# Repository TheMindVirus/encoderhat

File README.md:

# SparkFun RGB LED Push Encoder pHAT for Raspberry Pi (encoderphat)

## What is it?
It's an add-on board for the Raspberry Pi single board computer.

It makes use of 3x AVR Microcontrollers working together across I2C.

## What does it do?
It adds 3x customisable knobs with built-in multicoloured lights and push buttons.

It also gives you better access to the Pi's SPI Header Pins and lets you add custom firmware.

## Why do I need one?
It's great for small projects which need analog control, especially for music and science projects.

It can also combine with other HATs to form a keyboard scroller for when a USB keyboard is impractical.

## How do I get one?
It hasn't been released yet at the time of writing. I hope that SparkFun may pick it up and start producing it.

For now, these are my EAGLE design files. You may fork this repository and customise the design before you send it to The Fab.

## Useful Links
RGB LED Push Encoder: https://www.sparkfun.com/products/15141

ATMEGA328P-MU QFN32: https://statics3.seeedstudio.com/images/opl/datasheet/310010005.pdf

What is a Pi HAT?: https://www.raspberrypi.org/blog/introducing-raspberry-pi-hats/

## Enjoy!
Alastair Cota 18/07/2020

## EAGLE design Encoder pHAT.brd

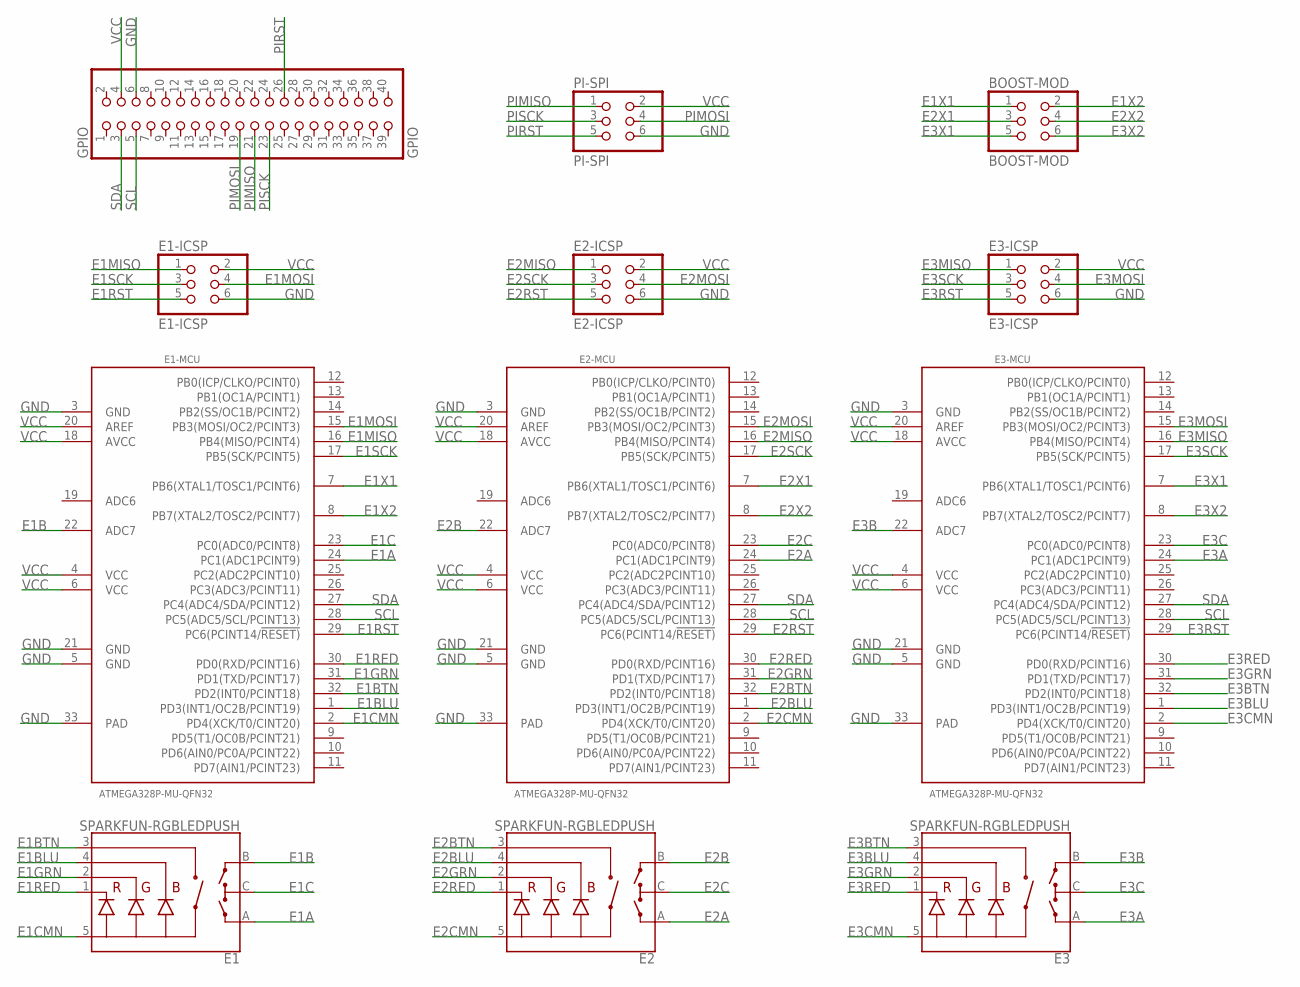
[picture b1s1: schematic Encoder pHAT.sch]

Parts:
BOOST-MOD: BOOST-MOD; 2X03
E1, E2, E3: SPARKFUN-RGBLEDPUSH; ENCODER_LED_3
E1-ICSP: E1-ICSP; 2X03
E1-MCU, E2-MCU, E3-MCU: ATMEGA328P-MU-QFN32; QFN32G-0.5-5X5MM
E2-ICSP: E2-ICSP; 2X03
E3-ICSP: E3-ICSP; 2X03
GPIO: GPIO; 2X20
PI-SPI: PI-SPI; 2X03

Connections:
E1A: E1.A, E1-MCU.24 (PC1(ADC1PCINT9))
E1B: E1.B, E1-MCU.22 (ADC7)
E1BLU: E1.4 (-B), E1-MCU.1 (PD3(INT1/OC2B/PCINT19))
E1BTN: E1.3 (SW), E1-MCU.32 (PD2(INT0/PCINT18))
E1C: E1.C, E1-MCU.23 (PC0(ADC0/PCINT8))
E1CMN: E1.5 (+), E1-MCU.2 (PD4(XCK/T0/CINT20))
E1GRN: E1.2 (-G), E1-MCU.31 (PD1(TXD/PCINT17))
E1MISO: E1-ICSP.1, E1-MCU.16 (PB4(MISO/PCINT4))
E1MOSI: E1-ICSP.4, E1-MCU.15 (PB3(MOSI/OC2/PCINT3))
E1RED: E1.1 (-R), E1-MCU.30 (PD0(RXD/PCINT16))
E1RST: E1-ICSP.5, E1-MCU.29 (PC6(PCINT14/!RESET))
E1SCK: E1-ICSP.3, E1-MCU.17 (PB5(SCK/PCINT5))
E1X1: BOOST-MOD.1, E1-MCU.7 (PB6(XTAL1/TOSC1/PCINT6))
E1X2: BOOST-MOD.2, E1-MCU.8 (PB7(XTAL2/TOSC2/PCINT7))
E2A: E2.A, E2-MCU.24 (PC1(ADC1PCINT9))
E2B: E2.B, E2-MCU.22 (ADC7)
E2BLU: E2.4 (-B), E2-MCU.1 (PD3(INT1/OC2B/PCINT19))
E2BTN: E2.3 (SW), E2-MCU.32 (PD2(INT0/PCINT18))
E2C: E2.C, E2-MCU.23 (PC0(ADC0/PCINT8))
E2CMN: E2.5 (+), E2-MCU.2 (PD4(XCK/T0/CINT20))
E2GRN: E2.2 (-G), E2-MCU.31 (PD1(TXD/PCINT17))
E2MISO: E2-ICSP.1, E2-MCU.16 (PB4(MISO/PCINT4))
E2MOSI: E2-ICSP.4, E2-MCU.15 (PB3(MOSI/OC2/PCINT3))
E2RED: E2.1 (-R), E2-MCU.30 (PD0(RXD/PCINT16))
E2RST: E2-ICSP.5, E2-MCU.29 (PC6(PCINT14/!RESET))
E2SCK: E2-ICSP.3, E2-MCU.17 (PB5(SCK/PCINT5))
E2X1: BOOST-MOD.3, E2-MCU.7 (PB6(XTAL1/TOSC1/PCINT6))
E2X2: BOOST-MOD.4, E2-MCU.8 (PB7(XTAL2/TOSC2/PCINT7))
E3A: E3.A, E3-MCU.24 (PC1(ADC1PCINT9))
E3B: E3.B, E3-MCU.22 (ADC7)
E3BLU: E3.4 (-B), E3-MCU.1 (PD3(INT1/OC2B/PCINT19))
E3BTN: E3.3 (SW), E3-MCU.32 (PD2(INT0/PCINT18))
E3C: E3.C, E3-MCU.23 (PC0(ADC0/PCINT8))
E3CMN: E3.5 (+), E3-MCU.2 (PD4(XCK/T0/CINT20))
E3GRN: E3.2 (-G), E3-MCU.31 (PD1(TXD/PCINT17))
E3MISO: E3-ICSP.1, E3-MCU.16 (PB4(MISO/PCINT4))
E3MOSI: E3-ICSP.4, E3-MCU.15 (PB3(MOSI/OC2/PCINT3))
E3RED: E3.1 (-R), E3-MCU.30 (PD0(RXD/PCINT16))
E3RST: E3-ICSP.5, E3-MCU.29 (PC6(PCINT14/!RESET))
E3SCK: E3-ICSP.3, E3-MCU.17 (PB5(SCK/PCINT5))
E3X1: BOOST-MOD.5, E3-MCU.7 (PB6(XTAL1/TOSC1/PCINT6))
E3X2: BOOST-MOD.6, E3-MCU.8 (PB7(XTAL2/TOSC2/PCINT7))
GND: E1-ICSP.6, E1-MCU.3 (GND), E1-MCU.5 (GND), E1-MCU.21 (GND), E1-MCU.33 (PAD), E2-ICSP.6, E2-MCU.3 (GND), E2-MCU.5 (GND), E2-MCU.21 (GND), E2-MCU.33 (PAD), E3-ICSP.6, E3-MCU.3 (GND), E3-MCU.5 (GND), E3-MCU.21 (GND), E3-MCU.33 (PAD), GPIO.6, PI-SPI.6
PIMISO: GPIO.21, PI-SPI.1
PIMOSI: GPIO.19, PI-SPI.4
PIRST: GPIO.26, PI-SPI.5
PISCK: GPIO.23, PI-SPI.3
SCL: E1-MCU.28 (PC5(ADC5/SCL/PCINT13)), E2-MCU.28 (PC5(ADC5/SCL/PCINT13)), E3-MCU.28 (PC5(ADC5/SCL/PCINT13)), GPIO.5
SDA: E1-MCU.27 (PC4(ADC4/SDA/PCINT12)), E2-MCU.27 (PC4(ADC4/SDA/PCINT12)), E3-MCU.27 (PC4(ADC4/SDA/PCINT12)), GPIO.3
VCC: E1-ICSP.2, E1-MCU.4 (VCC), E1-MCU.6 (VCC), E1-MCU.18 (AVCC), E1-MCU.20 (AREF), E2-ICSP.2, E2-MCU.4 (VCC), E2-MCU.6 (VCC), E2-MCU.18 (AVCC), E2-MCU.20 (AREF), E3-ICSP.2, E3-MCU.4 (VCC), E3-MCU.6 (VCC), E3-MCU.18 (AVCC), E3-MCU.20 (AREF), GPIO.4, PI-SPI.2

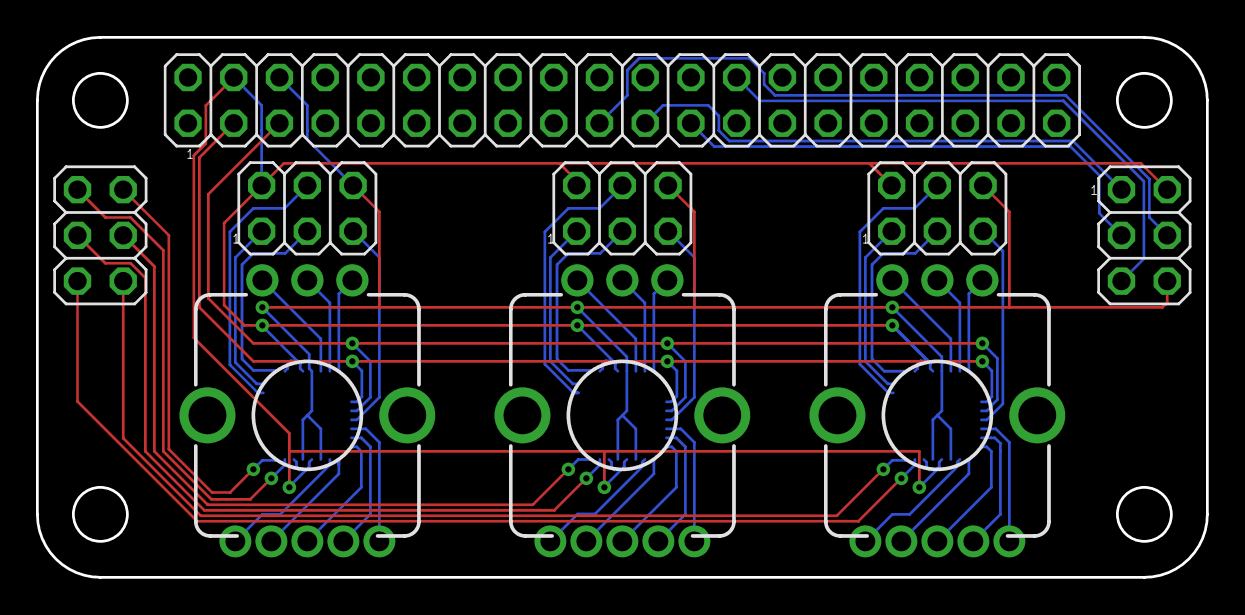
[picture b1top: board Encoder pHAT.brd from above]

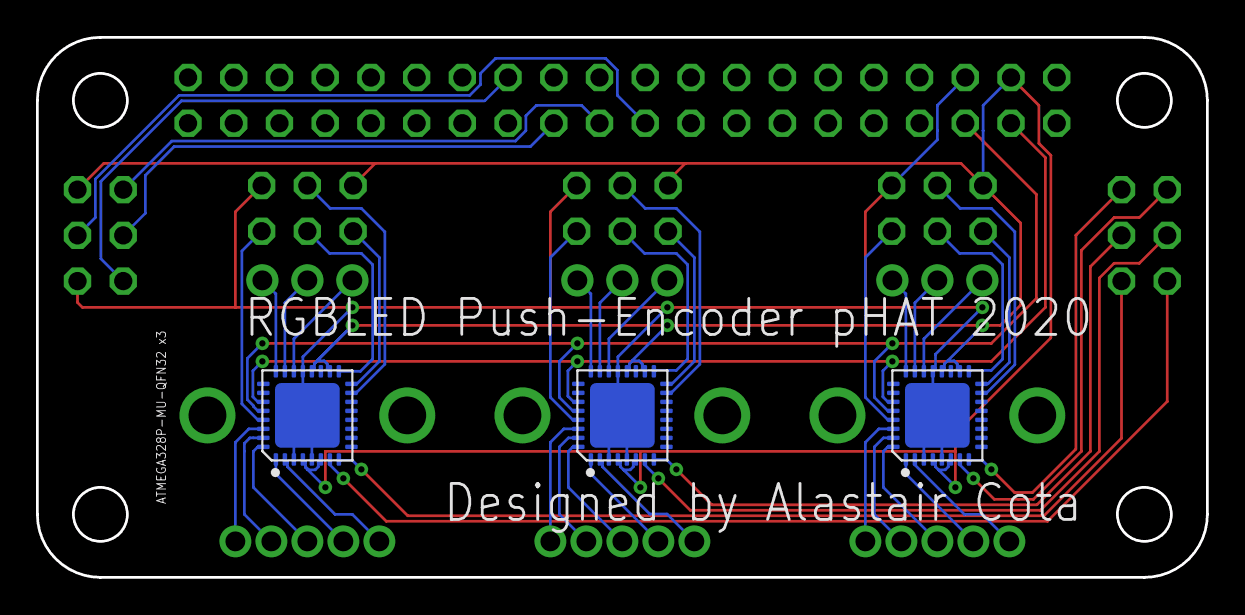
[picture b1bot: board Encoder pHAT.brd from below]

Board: 2 copper layers, 65.0 x 30.0 mm, 12 parts (3 on the bottom side), 50 nets.

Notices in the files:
parts and their libraries:
SparkFun-Switches: Licensing: Creative Commons ShareAlike 4.0 International - https://creativecommons.org/licenses/by-sa/4.0
